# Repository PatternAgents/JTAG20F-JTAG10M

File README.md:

JTAG20F-JTAG10M
===============

JTAG 20 Pin Female to JTAG 10 Pin Male Adapter

[  
*PatternAgents JTAG20F-JTAG10M*](http://www.patternagents.com/projects/JTAG20F-JTAG10M.html)

The PatternAgents JTAG20F-JTAG10M.

Features:

[  
*Licensing CC BY-NC-SA 4.0*](http://creativecommons.org/licenses/by-nc-sa/4.0/)

PatternAgents uses the increasingly popular business model called "Dual Licensing" 
in which both the open source software distribution mechanism and traditional commercial software distribution models are combined.

Open Source Projects:        

If you are developing and distributing open source applications under the Creative Commons CC BY-NC-SA 4.0, 
as published by the Creative Commons Foundation, then you are free to use the PatternAgents hardware/software under the CC BY-NC-SA 4.0 license. 
Please note that CC BY-NC-SA 4.0 requires that all modifications to the original code as well as all Derivative Works 
must also be released under the terms of the CC BY-NC-SA 4.0 license.

Closed Source Projects:

If you are developing and distributing traditional closed source or commercial applications, 
you must purchase a PatternAgents commercial use license, 
which is specifically designed for users interested in retaining the proprietary status of their designs and code. 
All PatternAgents commercial licenses expressly supersede the CC BY-NC-SA 4.0 license. 
This means that when you license the PatternAgents software under a commercial license, 
you specifically do not use the software under the CC BY-NC-SA 4.0 license and therefore you are not subject to any of its terms.
        
If you would like to use our designs for your own personal or educational use, have at it! 

Our public design repository is available at <a href="https://github.com/patternagents">Github</a>.

If you would like to produce our designs for commercial use, or as products for sale, 
please contact us to arrange for a Commercial Use license. We have many other designs, 
as well as options and extras that are not released publicly. 
We will also customize designs, firmware, and software for a reasonable fee, just contact us to discuss your requirements.

THIS SOFTWARE IS PROVIDED BY THE CONTRIBUTORS "AS IS" AND WITHOUT ANY EXPRESS OR IMPLIED WARRANTIES, 
INCLUDING, BUT NOT LIMITED TO, THE IMPLIED WARRANTIES OF MERCHANTABILITY AND FITNESS FOR A PARTICULAR PURPOSE ARE DISCLAIMED. 
IN NO EVENT SHALL THE COPYRIGHT OWNER OR CONTRIBUTORS BE LIABLE FOR ANY DIRECT, INDIRECT, INCIDENTAL, SPECIAL, EXEMPLARY, 
OR CONSEQUENTIAL DAMAGES (INCLUDING, BUT NOT LIMITED TO, PROCUREMENT OF SUBSTITUTE GOODS OR SERVICES; LOSS OF USE, DATA, 
OR PROFITS; OR BUSINESS INTERRUPTION) HOWEVER CAUSED AND ON ANY THEORY OF LIABILITY, WHETHER IN CONTRACT, 
STRICT LIABILITY, OR TORT (INCLUDING NEGLIGENCE OR OTHERWISE) ARISING IN ANY WAY OUT OF THE USE OF THIS SOFTWARE, 
EVEN IF ADVISED OF THE POSSIBILITY OF SUCH DAMAGE. 

-------------------------------------------------------------------------------------------

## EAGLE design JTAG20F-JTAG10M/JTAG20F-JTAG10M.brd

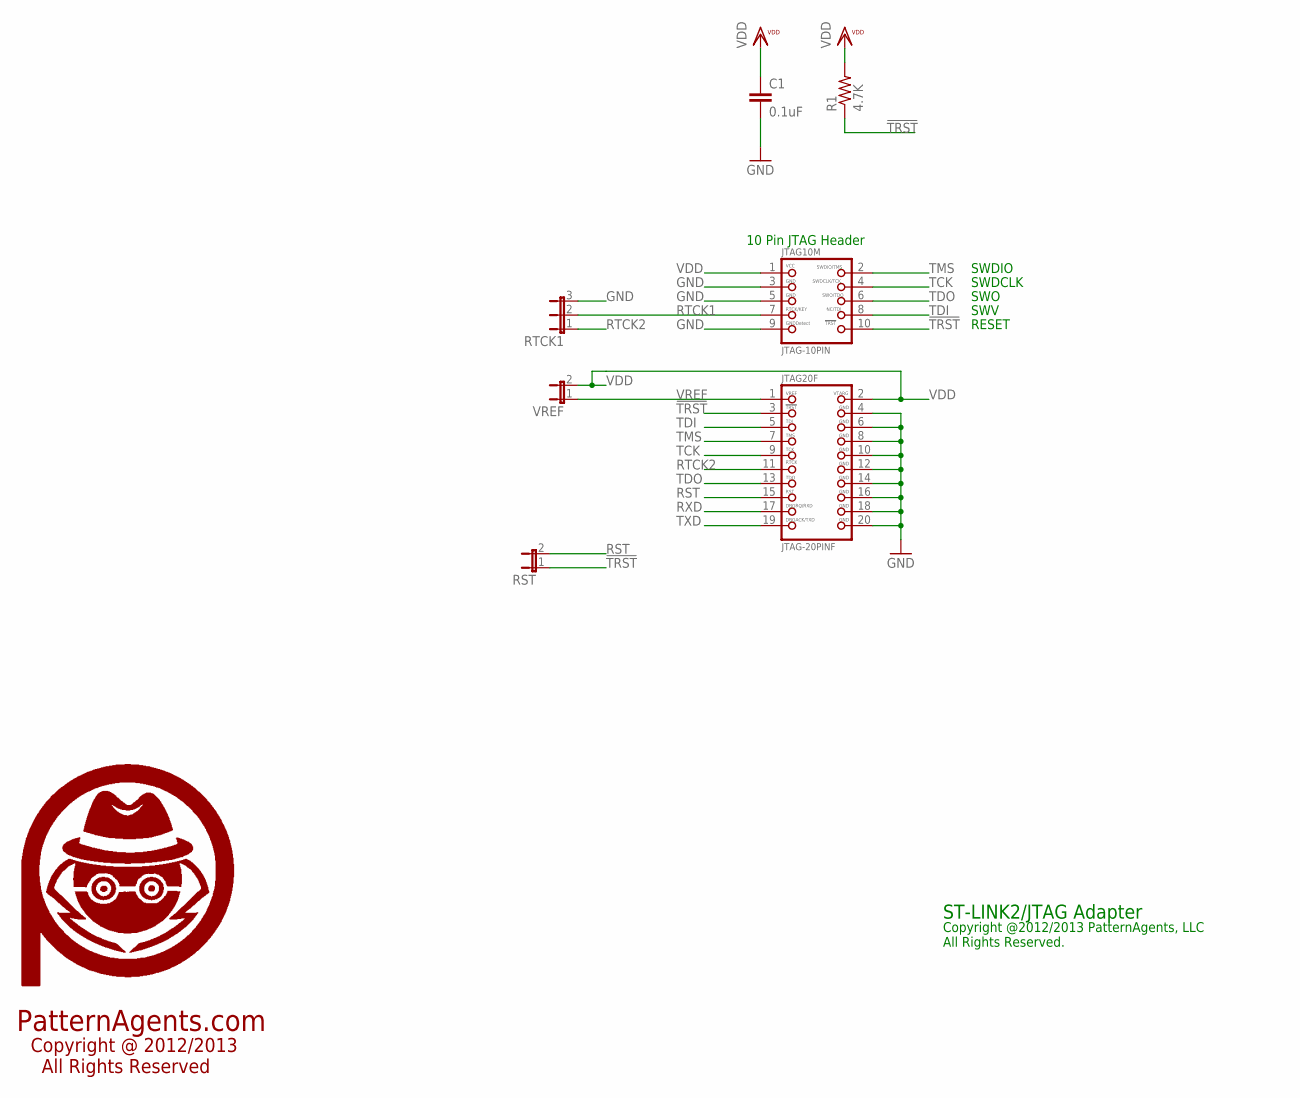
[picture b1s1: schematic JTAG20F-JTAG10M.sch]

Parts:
C1: 0.1uF; 0603-CAP
JTAG10M: JTAG-10PIN; 2X05_1.27MM_SMT
JTAG20F: JTAG-20PINF; 2X10F_2.54MM_PTH
R1: 4.7K; 0603-RES
RST: JUMPER2
RTCK1: JUMPER3
U$2: PA_LOGO_SYMLARGE; PA_LOGO_AGENT_LRG_SYM
VREF: JUMPER2

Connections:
!TRST: JTAG10M.10, JTAG20F.3, R1.1, RST.1
GND: C1.2, JTAG10M.3, JTAG10M.5, JTAG10M.9, JTAG20F.4, JTAG20F.6, JTAG20F.8, JTAG20F.10, JTAG20F.12, JTAG20F.14, JTAG20F.16, JTAG20F.18, JTAG20F.20, RTCK1.3
RST: JTAG20F.15, RST.2
RTCK1: JTAG10M.7, RTCK1.2
RTCK2: JTAG20F.11, RTCK1.1
RXD: JTAG20F.17
TCK: JTAG10M.4, JTAG20F.9
TDI: JTAG10M.8, JTAG20F.5
TDO: JTAG10M.6, JTAG20F.13
TMS: JTAG10M.2, JTAG20F.7
TXD: JTAG20F.19
VDD: C1.1, JTAG10M.1, JTAG20F.2, R1.2, VREF.2
VREF: JTAG20F.1, VREF.1

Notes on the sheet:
PatternAgents.com
Copyright @ 2012/2013 All Rights Reserved
ST-LINK2/JTAG Adapter
Copyright @2012/2013 PatternAgents, LLC All Rights Reserved.
SWDIO
SWDCLK
RESET
10 Pin JTAG Header
SWO
SWV

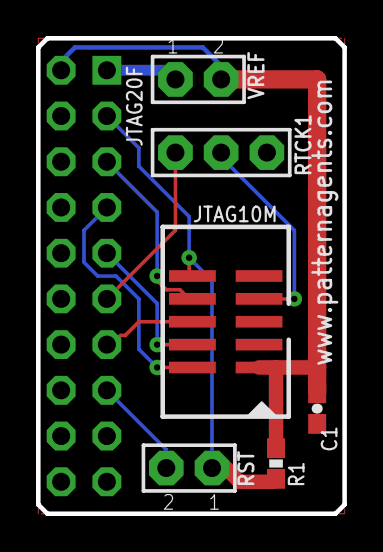
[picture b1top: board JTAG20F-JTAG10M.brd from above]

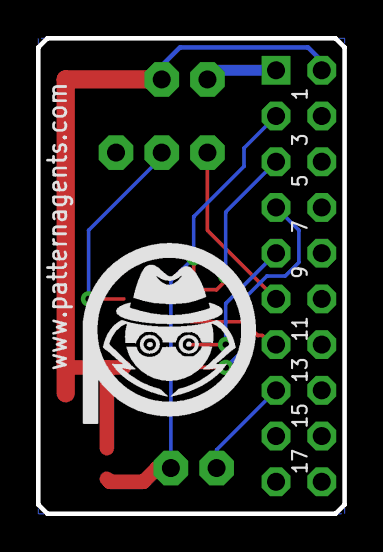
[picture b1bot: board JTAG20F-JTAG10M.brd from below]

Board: 2 copper layers, 17.0 x 26.4 mm, 8 parts (2 on the bottom side), 11 nets.

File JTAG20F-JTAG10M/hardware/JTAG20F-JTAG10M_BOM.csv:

"Part";"Value";"Device";"Package";"Description";"";
"C1";"0.1uF";"CAP0603-CAP";"0603-CAP";"Capacitor";"";
"JTAG10M";"JTAG-10PIN";"JTAG-10PINSMD";"2X05_1.27MM_SMT";"JTAG 10 Pin (SWD) Programming Connector";"";
"JTAG20F";"JTAG-20PINF";"JTAG-20PINF";"2X10F_2.54MM_PTH";"JTAG 20 Pin Programming Connector";"";
"R1";"4.7K";"RESISTOR_SFE0603-RES";"0603-RES";"Resistor";"";
"RST";"";"JUMPER2";"JUMPER2";"Jumper 2 Pin";"";
"RTCK1";"";"JUMPER3";"JUMPER3";"Jumper 3 Pin";"";
"U$2";"PA_LOGO_SYMLARGE";"PA_LOGO_SYMLARGE";"PA_LOGO_AGENT_LRG_SYM";"PatternAgents Logo Symbol";"";
"VREF";"";"JUMPER2";"JUMPER2";"Jumper 2 Pin";"";

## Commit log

2014-04-17 add eagle files

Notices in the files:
parts and their libraries:
PatternAgents-Logos: License : http://creativecommons.org/licenses/by-sa/3.0
(Creative Commons 3.0)
